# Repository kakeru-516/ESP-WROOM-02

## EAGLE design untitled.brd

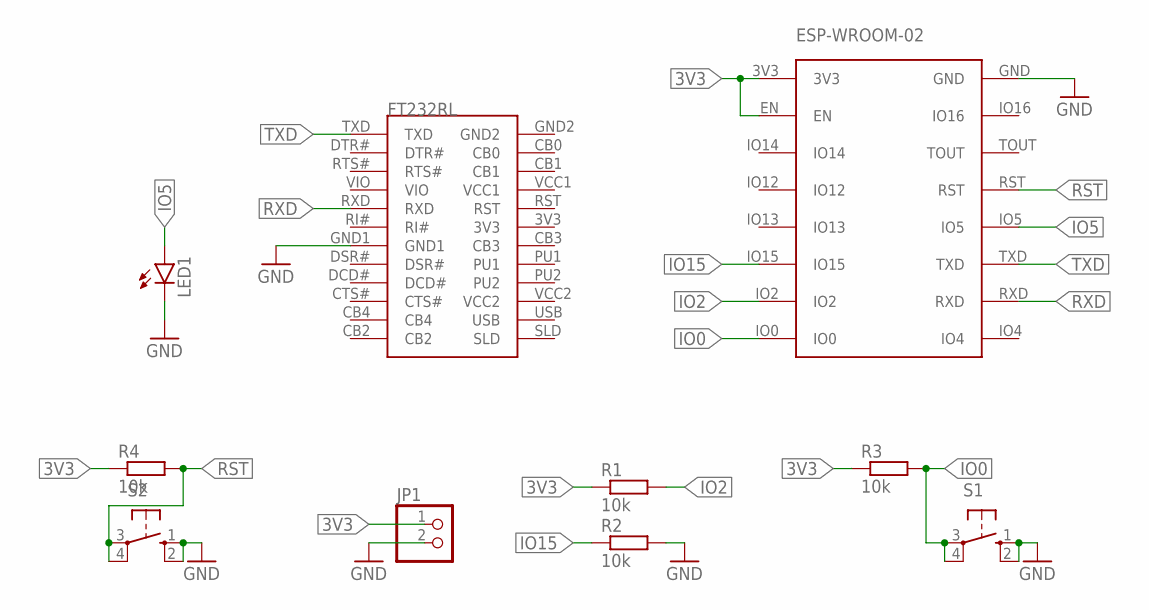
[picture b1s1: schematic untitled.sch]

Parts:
ESP-WROOM-1: ESP-WROOM-02
FT232RL1: FT232RL
JP1: PINHD-1X2; 1X02
LED1: LED5MM
R1, R2, R3, R4: 10k; 0204/7
S1, S2: 10-XX; B3F-10XX

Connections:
3V3: ESP-WROOM-1.3V3, ESP-WROOM-1.EN, JP1.1, R1.1, R3.1, R4.1
GND: ESP-WROOM-1.GND, FT232RL1.GND1, JP1.2, LED1.K (C), R2.2, S1.1 (S), S1.2 (S1), S2.1 (S), S2.2 (S1)
IO0: ESP-WROOM-1.IO0, R3.2, S1.3, S1.4 (P1)
IO2: ESP-WROOM-1.IO2, R1.2
IO5: ESP-WROOM-1.IO5, LED1.A
IO15: ESP-WROOM-1.IO15, R2.1
RST: ESP-WROOM-1.RST, R4.2, S2.3, S2.4 (P1)
RXD: ESP-WROOM-1.RXD, FT232RL1.RXD
TXD: ESP-WROOM-1.TXD, FT232RL1.TXD

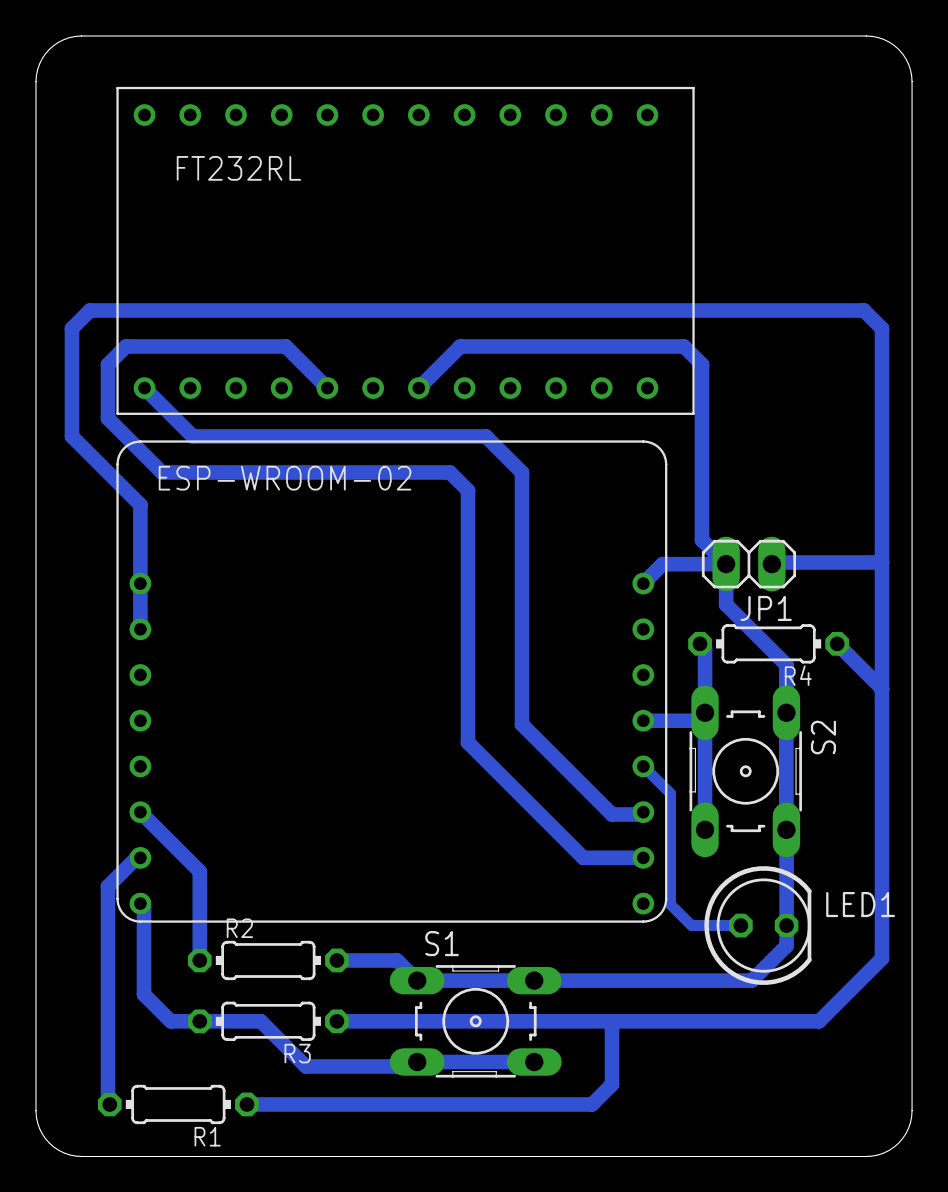
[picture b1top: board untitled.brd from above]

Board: 2 copper layers, 48.7 x 62.2 mm, 10 parts (0 on the bottom side), 9 nets.

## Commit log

2022-08-07 Maybe Complete
